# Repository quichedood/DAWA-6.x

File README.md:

# DAWA-6.x - FR (See below for US)

Site web officiel (FR) : http://dawa.panik-po.com/

DAWA est un système de chronométrage et d'acquisition de données pour votre moto.
Il enregistre les données 10x par seconde dans un fichier CSV.

# Q&A rapide
* __Comment sont récupérées les données ?__  
Pas de prise OBD, protocole trop lent sur ma "veille" moto de 2009. Je récupère les informations directement sur le faisceau du calculateur.
Chaque moto est différente, il faudra sur une autre moto :
    - Identifier les signaux (RPM, vitesse, position poignée de gaz, rapport engagé et frein)
    - Vérifier la forme des signaux (RPM = signal carré, poignée de gaz = signal analogique, etc.)
    - Eventuellement adapter le code au niveau de la programmation si le signal est complètement différent

* __Je peux l'assembler moi même ?__  
Aucun problème, attention néanmoins, il vous faut au minimum :
    - Le circuit imprimé (je peux le fournir, j'en ai quelques uns en stock)
    - Un programmateur pour les 2 µproc Atmel SAMD21 (Atmel ICE BASIC par exemple)
    - Une station de soudure à l'air chaud (indispensable pour souder l'IMU)

* __Combien ça coute ?__  
Grossièrement, voici ce que ça me coûte :
    - PCB : ~10€
    - Composants : ~90€
    - Autres (impression 3D, résine pour les sondes de t°, la journée passée à assembler un exemplaire) : à vous de juger

Certes, ça reste moins cher que ce que l'on peut trouver dans le commerce (Starlane, Alfano, 3DMS) mais ce n'est clairement pas comparable.  
Vous voulez un vrai chrono, utilisable à la sortie de sa boite, passez votre chemin et dirigez vous vers les produits du commerce.  
Vous voulez un maximum de fonctionnalités, pouvoir faire évoluer un projet libre et avez quelques notions en électronique/développement, ce projet est pour vous :)

# Les nouveautés de la v6
* __Nouveau circuit imprimé__ : DAWA v6 est désormais un circuit imprimé autonome (puce Atmel SAMD21 comme l'Arduino M0). La v5 était un module qui se branchait sur un Arduino M0
* __Nouveau capteur de position__ : Le capteurs 9 axes MPU-9250 est maintenant utilisé. Ce capteur est monté sur un circuit imprimé secondaire avec son propre µproc (Atmel SAMD21)
* __Nouvel écran OLED__ : Un peu plus grand (1.3" vs 0.96"). Le connecteur d’écran (SPI) est compatible avec les écrans LCD couleur 2,4" 240x320
* __Nouveau boitier__ : Un tout nouveau boîtier imprimé en 3D
* __Autodetection des capteurs__ : Les capteurs de température infrarouges sont maintenant détectés automatiquement
* __Navigation__ : Ajout d'un système de menu de navigation et 4 boutons pour permettre la configuration et l'utilisation sans smartphone ni Bluetooth
* __LEDs__ : Ajout de 4 LEDs pour des événements spécifiques (meilleur temps au tour par exemple)
* __Connecteurs__ : tous les connecteurs sont maintenant du même côté (en bas), le connecteur GPS est maintenant de type SMA (à visser)
* __Batterie GPS__ : Batterie rechargeable LIR 2025

# Quelles informations sont enregistrées ?
* __Acquisition de données bruts__ : Sur les motos Triumph et beaucoup d’autres, les valeurs du calculateur peuvent être lues directement (j’utilise personnellement: RPM, vitesse, position poignée de gaz, rapport engagé et frein)
* __Atitude de la moto__ : Un capteur à 9 axes (MPU-9250) est utilisé pour stocker les G et j'espère que bientôt, le roulis et le tangage
* __Position de la moto__ : Une puce GPS UBLOX 10Hz récupère les coordonnées GPS en temps réel
* __Température infrarouge__ : Vous pouvez brancher jusqu'à 6 capteurs de température infrarouge (pneus ou t° au sol, par exemple).
* __Entrées additionnelles__ : Vous pouvez mesurer 2 entrées analogiques et 2 entrées numériques supplémentaires (capteurs de suspension par exemple)

# Où est-ce enregistré ?
Tout est stocké sur une carte micro SD.  
10 fois par seconde, une nouvelle ligne est créée dans un fichier CSV. Cette ligne contient toutes les valeurs de données séparées par un point-virgule.  
Les valeurs actuelles sont affichées en temps réel sur l’écran OLED joint.

# Peut-il être utilisé comme un chronomètre ?
OUI ! Depuis la v4 et l'intégration d'une puce GPS 10Hz, des fonctions de chronométrage sont disponibles.

# Comment ça marche ?
Rien de plus simple !  
Un bouton pour démarrer l'enregistrement et un pour l'arrêter :)  
Un fichier CSV est créé à chaque nouvel enregistrement.  

# Qu'en est-il des fonctions de chronométrage
Un peu plus compliqué, vous devez mettre un fichier nommé "TRACKS.CSV" sur la carte SD.  
Ce fichier contiendra le nom du circuit et les coordonnées de la ligne d'arrivée, une ligne par circuit:  
`<trackname>;<finishline lat. A>;<finishline lon. A>;<finishline lat. B>;<finishline lon. B>`  
`CAROLE;489799930;25224350;489800230;25226330`  
Pour conserver la précision, la latitude et la longitude doivent être converties en nombres entiers (multiplier par 10 000 000).  
Au début de l’enregistrement, la piste la plus proche est automatiquement choisie.

# Vous avez dit Bluetooth?
La connexion Bluetooth est utile dans ces 2 cas:  
- Vous venez de terminer votre session sur piste et vous voulez connaître les temps/meilleurs tours  
- Avant d'utiliser DAWA, certains paramètres peuvent être ajustés, utilisez la console Bluetooth pour les configurer !  
  
J'utilise "Serial Bluetooth Terminal" sur Androïd. Connectez-vous et tapez "help" pour voir toutes les commandes disponibles

# Evolutions
* __Temps intermédiaire__ : Ajout de la gestion des temps intermédiaires

# Bugs connus
* __Angle d'inclinaison__ : Le composant est présent, l'algorithme aussi mais les valeurs dérivent dans le temps. C'est une problématique récurrente.

# Contenu du référentiel
* /3D Case - Pièces Fusion 360 et fichiers STL pour l'impression 3D
* /Arduino - Le fichier .ino que vous devez insérer dans l’Arduino M0
* /Documentation - Quelques informations sur ce projet (FR)
* /Eagle - Tous les fichiers Eagle (schémas, PCB/Gerber, bibliothèques, liste de composants)

# DAWA-6.x - US

French official website project : http://dawa.panik-po.com/

DAWA is an Arduino datalogger and laptimer for your motorbike.
It records 10 times per seconds in a CSV file lots of information.

# What's new in v6
* __New PCB__ : DAWA v6 is now a standalone PCB (Atmel SAMD21 chip like Arduino M0). v5 was a shield which needs an Arduino M0
* __New IMU__ : MPU-9250 is now used. This IMU is on a secondary PCB with his own µproc (Atmel SAMD21)
* __New OLED screen__ : A little bit bigger (1.3" vs 0.96"). The screen connector (SPI) is compatible with 2.4" 240x320 color LCD
* __New enclosure__ : A brand new 3D printed enclosure
* __Sensors autodetection__ : Infrared temperature sensors are now autodetected
* __Navigation__ : Add a navigation menu system and 4 buttons to allow configuration and use without smartphone and Bluetooth
* __Lights__ : Add 4 LEDS for specific events (best time on lap for example)
* __Connectors__ : All connectors are now on the same side (bottom), GPS connector is now SMA
* __GPS battery__ : Rechargeable LIR 2025 Battery

# What information is logged ?
* __Raw data acquisition__ : On Triumph bikes and many others, ECU values can be directly read (I personnaly use : RPM, SPEED, GEAR POSITION, THROTTLE and BRAKE state)
* __Environement values__ : A 9-axis sensor (MPU-9250) is used to store G-forces and I hope soon, roll and pitch
* __Position values__ : A UBLOX 10Hz GPS chip gets realtime coordinates
* __Infrared temperatures__ : You can plug up to 6 infrared temperature sensors (tyres or ground t° for example)
* __Additional inputs__ : You can measure 2 analog inputs and 2 digital inputs (suspension sensors for exemple)

# Where is it logged ?
Everything is stored on a micro SD card.  
10 times per seconds, a new line is created in a CSV file. This line contains every data values separated by a semicolon.  
Current values are displayed in realtime on the OLED screen attached.

# Could it be used as a laptimer ?
YES ! Since v4 and the integration of a 10Hz GPS chip, laptimer functions are available.

# How does it work ?
I couldn't make it easier !  
Press the button start recording, press again stop recording :)  
One CSV file is created on each new record.

# What about laptimer functions
A little bit more difficult, you have to put a file named "TRACKS.CSV" on the sdcard.  
This file will contain track name and finishline coordinates, one line per track :  
`<trackname>;<finishline lat. A>;<finishline lon. A>;<finishline lat. B>;<finishline lon. B>`  
`CAROLE;489799930;25224350;489800230;25226330`  
To keep precision, latitude and longitude should be converted to integers (multiply by 10 000 000).  
When start recording the closer track is automatically chosen.

# You said Bluetooth ?
Bluetooth connection is usefull in these 2 cases :
- You just finish your track session and want to know lap times / best lap
- Before using DAWA, some parameters could be adjusted, use the bluetooth console to setup them !

I'm using "Serial Bluetooth Terminal" on Androïd. Connect and type "help" to view all available commands

# What's next  
* __Laptimer split time__ : Add split time management

# Known bugs
* __Lean angle__ : Seems easy but in fact very complicated to obtain good values without drift

# Repository Contents
* /3D Case - Fusion 360 parts and STL files for 3D printing
* /Arduino - The .ino file you need to put in the Arduino M0
* /Documentation - Some brief explanations about this shield (french - not translated)
* /Eagle - All Eagle files (schematics, PCB/Gerber, libraries, parts list)

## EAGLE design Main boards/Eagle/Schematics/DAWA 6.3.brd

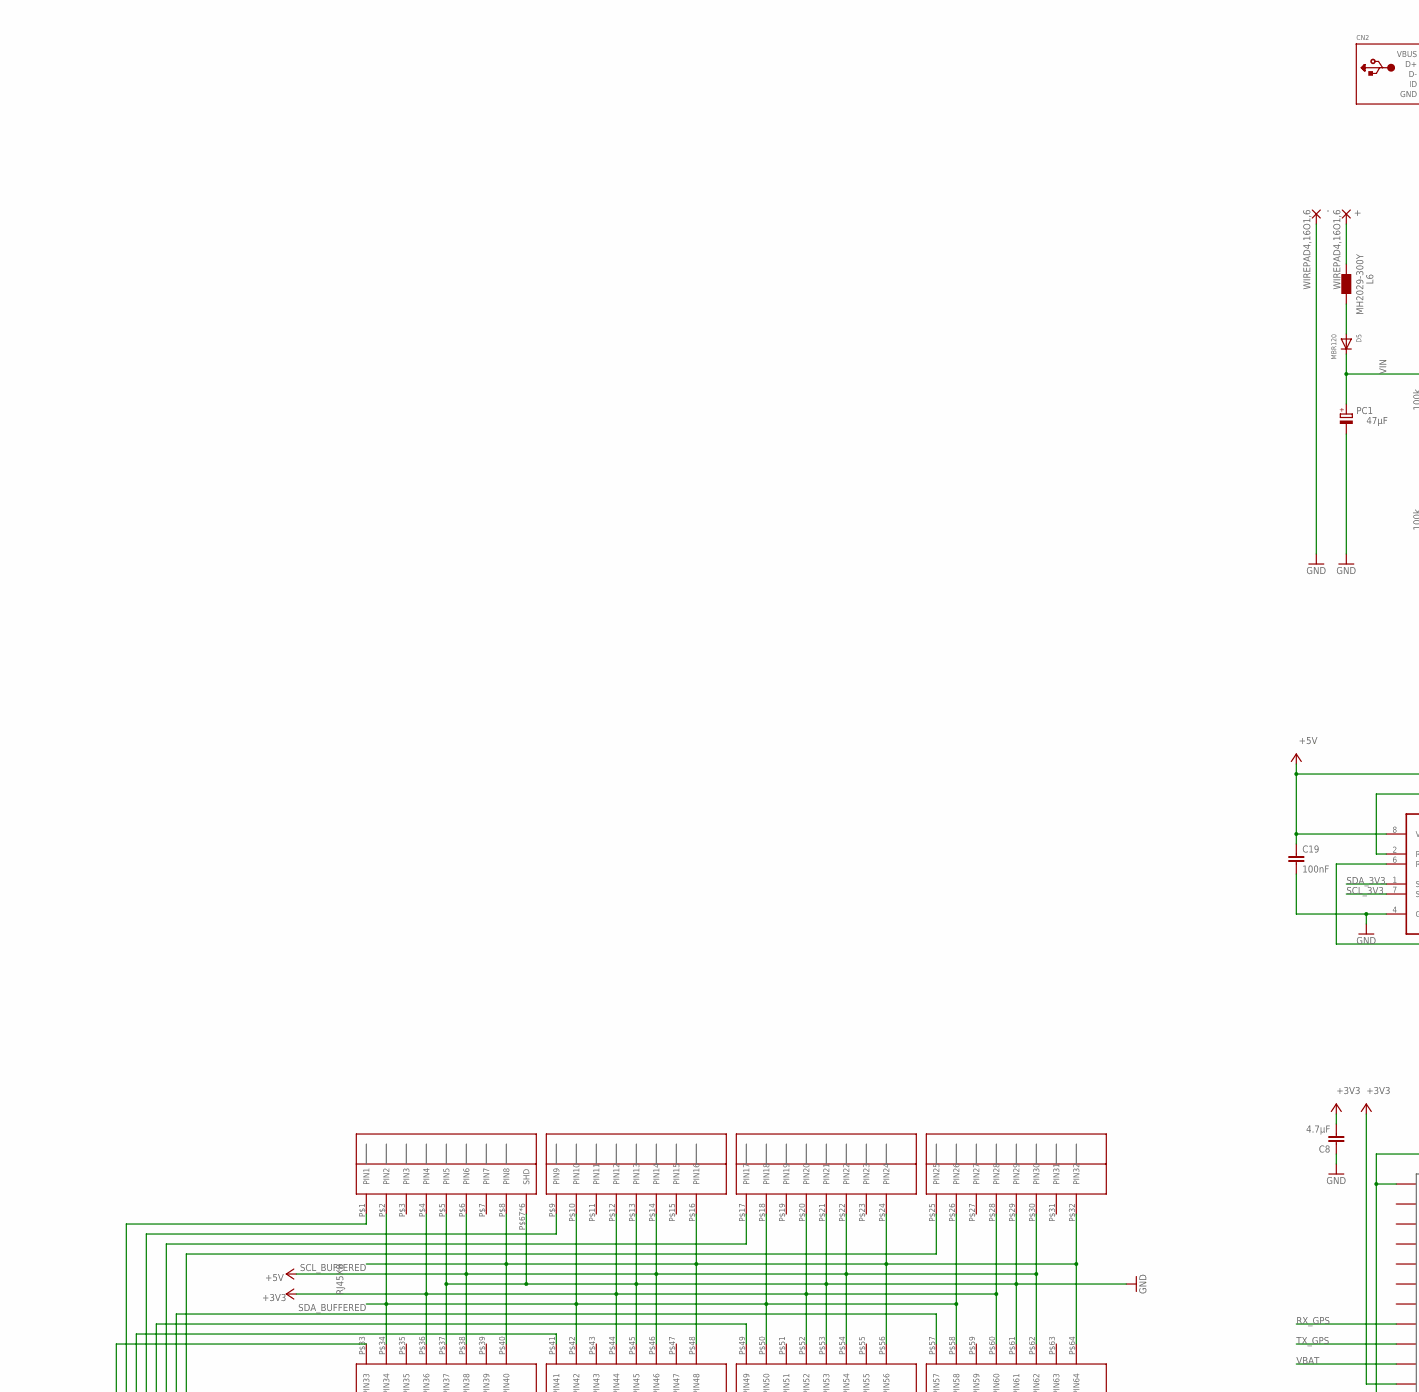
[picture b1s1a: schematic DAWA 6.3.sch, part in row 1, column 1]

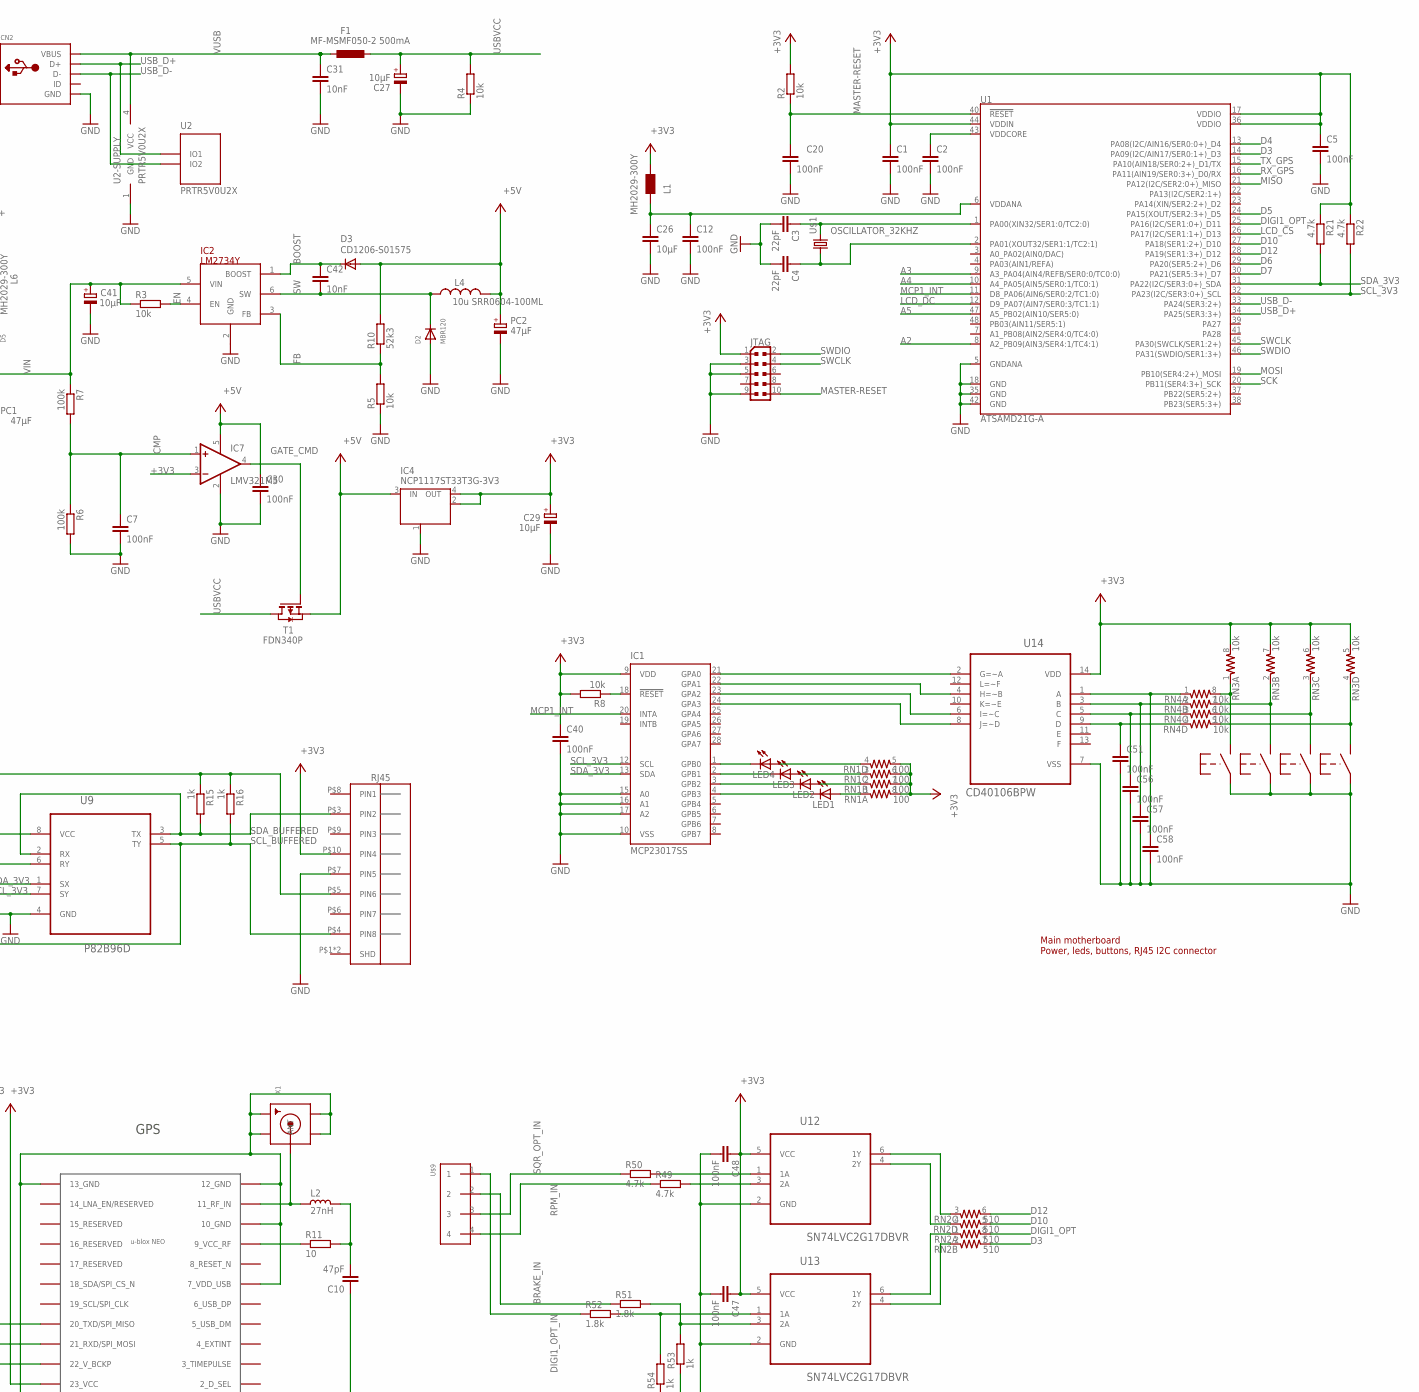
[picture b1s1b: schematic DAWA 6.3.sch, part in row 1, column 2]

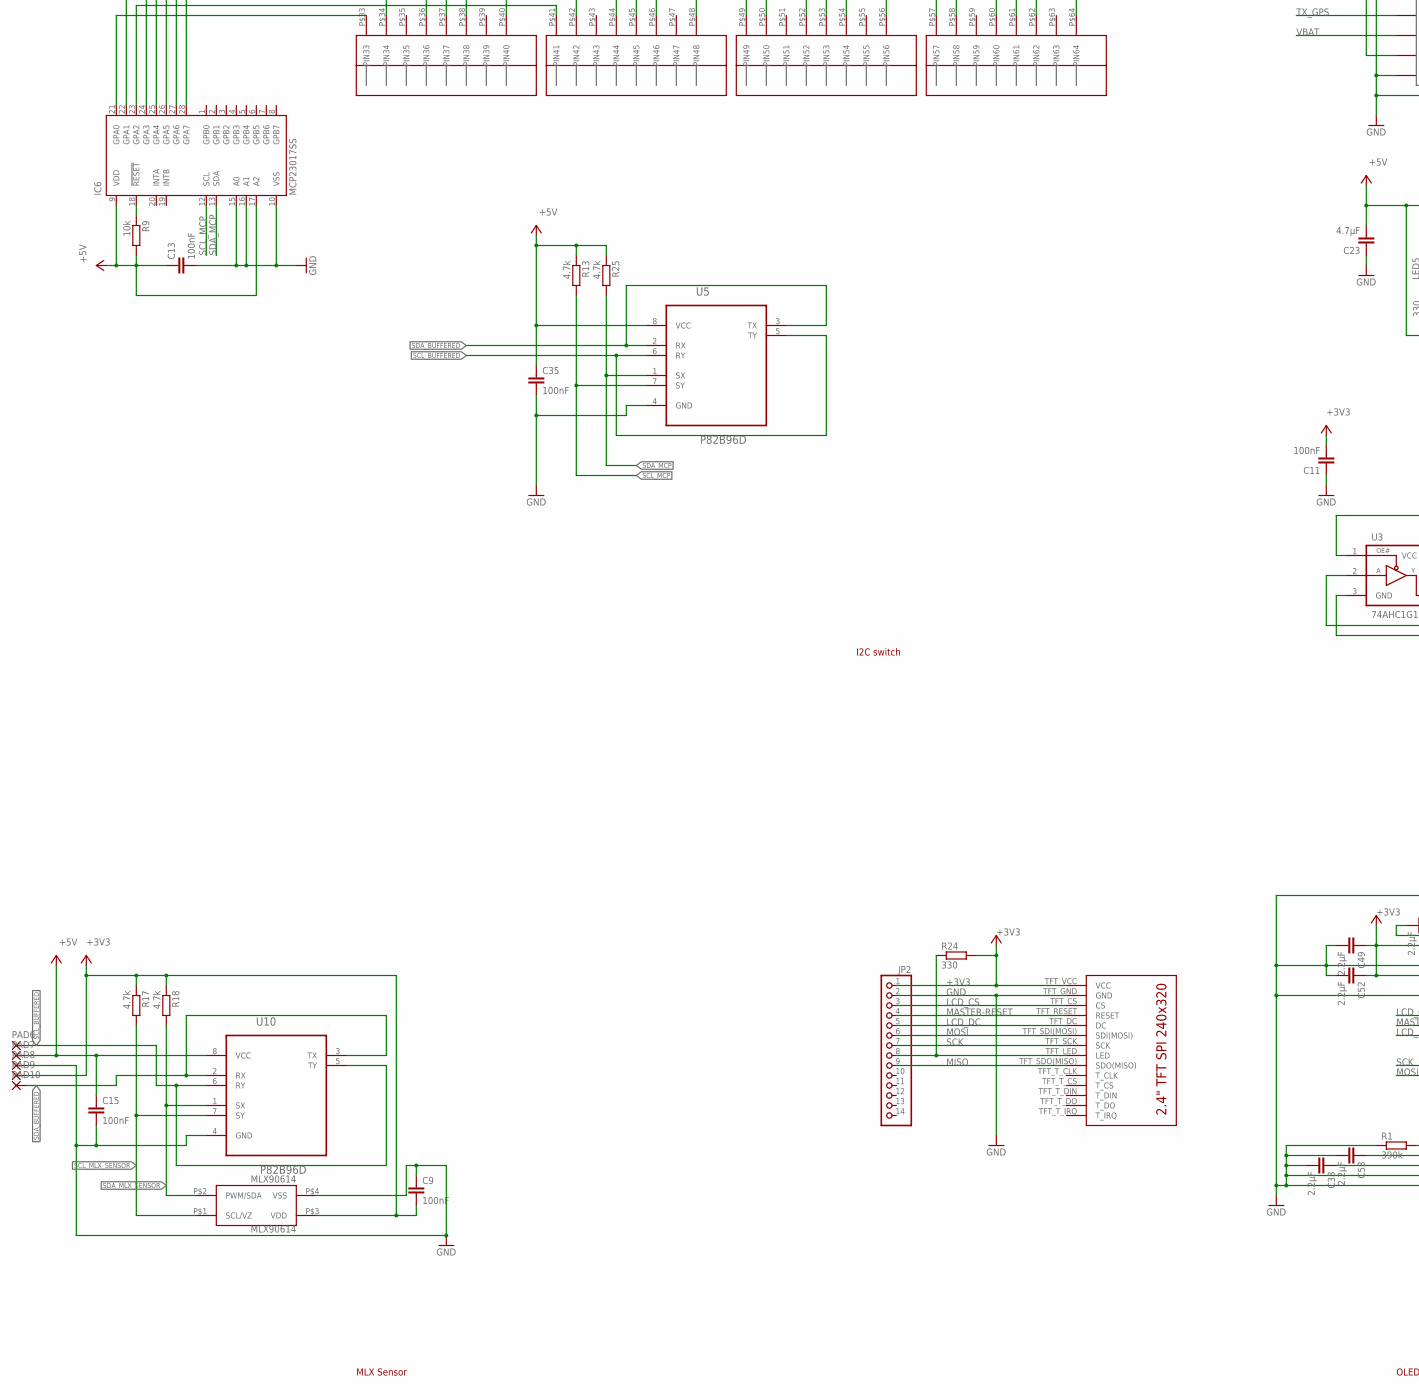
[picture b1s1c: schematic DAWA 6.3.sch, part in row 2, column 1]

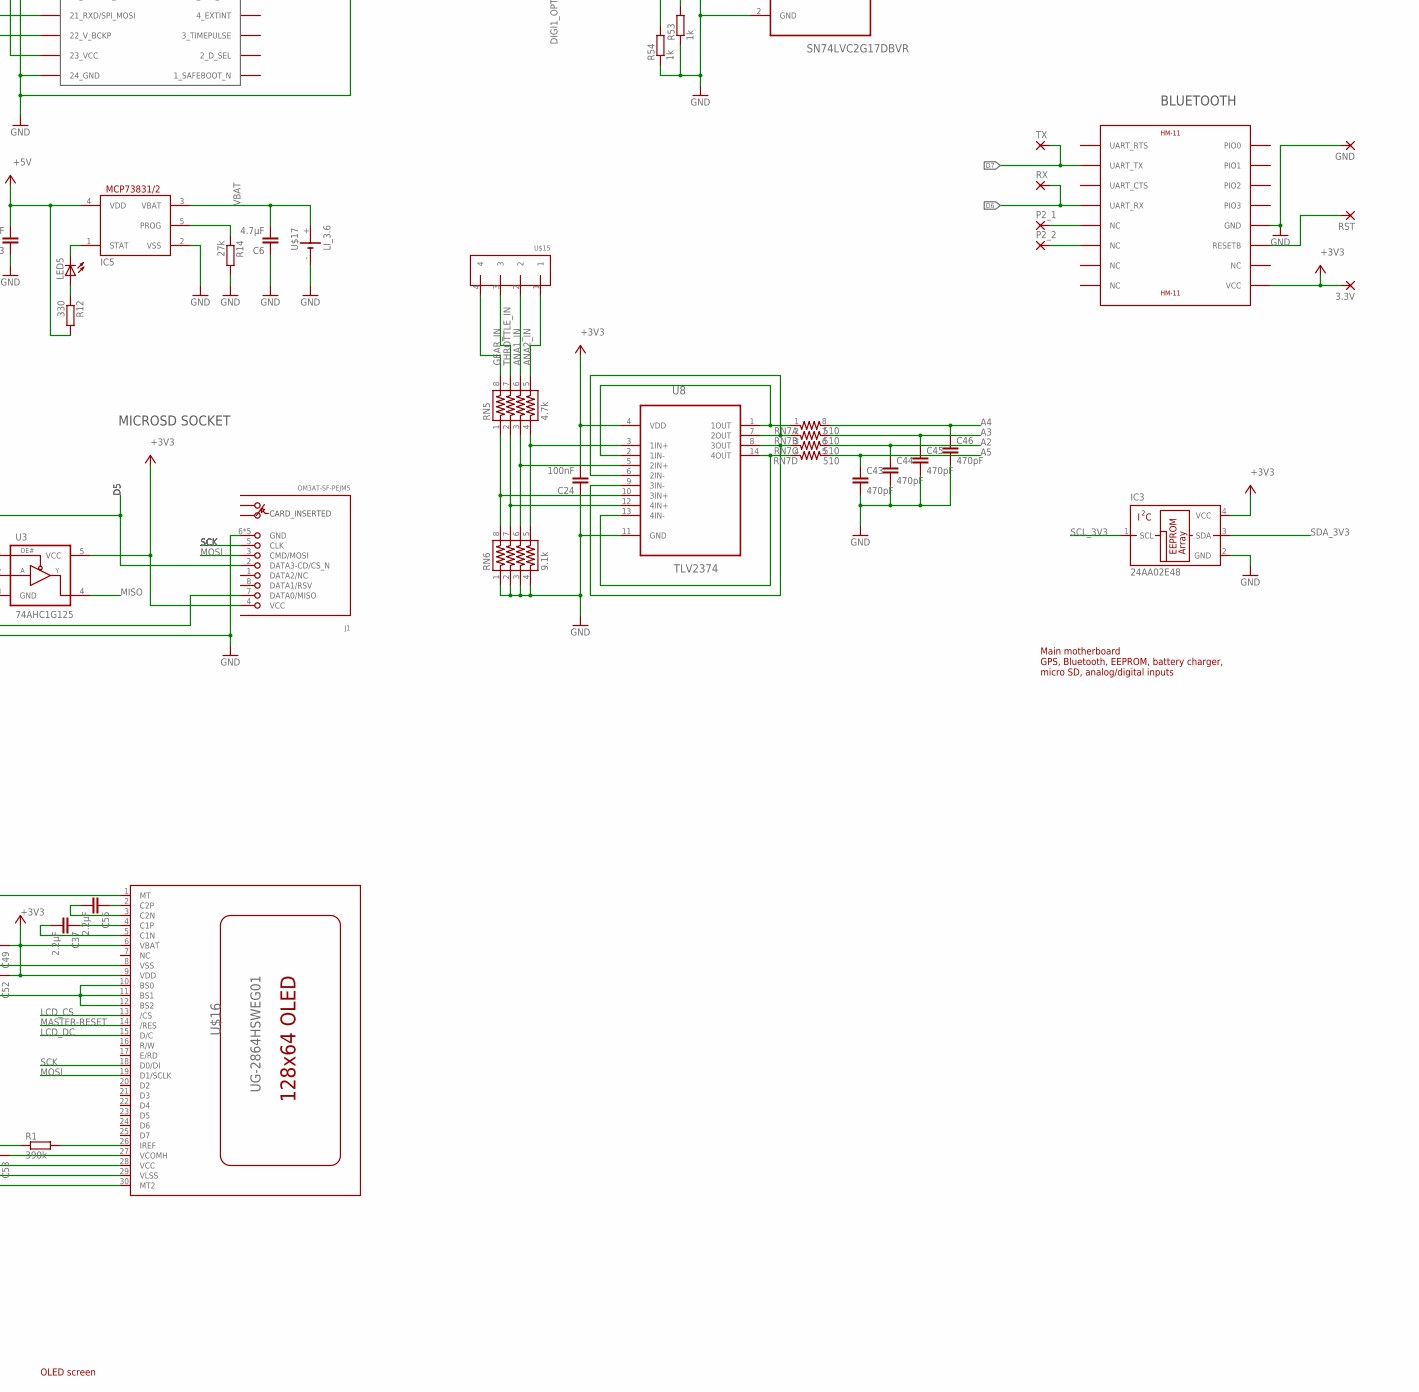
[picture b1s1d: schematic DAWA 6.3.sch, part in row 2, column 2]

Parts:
3.3V: WIREPADSMD1,27-254; SMD1,27-2,54
+: WIREPAD4,16O1,6; 4,16O1,6
-: WIREPAD4,16O1,6; 4,16O1,6
C1, C2, C5, C7, C9, C11, C12, C13, C15, C19, C20, C24, C30, C35, C40, C47, C48, C51, C56, C57, C58: 100nF; C0603
C3, C4: 22pF; C0603
C6, C8, C23: 4.7µF; C0603
C10: 47pF; C0603
C26: 10µF; C0805
C27, C29, C41: 10µF; SMC_B
C31, C42: 10nF; C0603
C33, C37, C49, C52, C53, C55: 2.2µF; C0603
C43, C44, C45, C46: 470pF; C0603
CN2: USB; USB-MINIB-DAWA
D2, D5: MBR120; SOD-123FL
D3: CD1206-S01575; MINIMELF
F1: MF-MSMF050-2 500mA; L1812
GND: WIREPADSMD1,27-254; SMD1,27-2,54
IC1, IC6: MCP23017SS; SSOP28
IC2: LM2734Y; SOT23-6
IC3: 24AA02E48; SOT23-5L
IC4: NCP1117ST33T3G-3V3; SOT223
IC5: MCP73831/OT; SOT23-5L
IC7: LMV321M5; SOT23-5
J1: DM3AT-SF-PEJM5
JP2: PINHD-1X14-CB; 1X14-CB
JTAG: PINHEAD_PINHD-2X5PASSO127; PINHEAD_2X05_127
L1, L6: MH2029-300Y; 0805
L2: 27nH; L0603
L4: 10u SRR0604-100ML; SRR0604
LED1, LED2, LED3, LED4, LED5: LEDCHIPLED_1206; CHIPLED_1206
MLX90614: MLX90614; TO-39
P2_1, P2_2: WIREPADSMD1,27-254; SMD1,27-2,54
PAD6, PAD7, PAD8, PAD9, PAD10: WIREPAD1,6/0,9; 1,6/0,9
PC1, PC2: 47µF; PANASONIC_D
R1: 390k; R0603
R2, R3, R4, R5, R8, R9: 10k; R0603
R6, R7: 100k; R0603
R10: 52k3; R0603
R11: 10; R0603
R12, R24: 330; R0603
R13, R17, R18, R21, R22, R25, R49, R50: 4.7k; R0603
R14: 27k; R0603
R15, R16, R53, R54: 1k; R0603
R51, R52: 1.8k; R0603
RJ45_MAIN_BOARD: RJ45
RN1: 100; 742-8NS
RN2, RN7: 510; 742-8NS
RN3, RN4: 10k; 742-8NS
RN5: 4.7k; 742-8NS
RN6: 9.1k; 742-8NS
RST: WIREPADSMD1,27-254; SMD1,27-2,54
RX: WIREPADSMD1,27-254; SMD1,27-2,54
T1: FDN340P; SOT-23
TX: WIREPADSMD1,27-254; SMD1,27-2,54
U1: ATSAMD21G-A; TQFP-48
U2: PRTR5V0U2X; SOT-143B
U3: 74AHC1G125; SOT23-5
U5, U9, U10: P82B96D; SOIC127P600X175-8N
U8: TLV2374; SOP65P640X120-14N
U12, U13: SN74LVC2G17DBVR; SOT95P280X145-6N
U14: CD40106BPW; SOP65P640X120-14N
U$1: OSCILLATOR_32KHZ; OSCILLATOR_SMD
U$2: HM-11
U$3: NEO-M8
U$4: TFT_2.4
U$5, U$6, U$7, U$8: SKPMAPE10
U$9, U$15: 4_PIN_JST-XH-SMD
U$16: UG-2864HSWEG01; 1X30-0.7MM
U$17: LI_3.6
U$18: RJ45X8
X1: SMACONNECTOR_EDGE; SMA_EDGELAUNCH

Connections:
+3V3: 3.3V.1, C1.1, C5.1, C8.2, C9.2, C11.2, C24.2, C29.+, C40.1, C47.1, C48.1, C49.1, C52.1, IC1.9 (VDD), IC3.4 (VCC), IC4.2 (OUT), IC4.4 (OUT), IC7.3 (-IN), J1.4 (VCC), JP2.1, JTAG.1, L1.1, MLX90614.P$3 (VDD), PAD9.1, R2.2, R8.2, R17.1, R18.1, R21.1, R22.1, R24.2, RJ45_MAIN_BOARD.P$10 (PIN4), RN1.5 (2), RN1.6 (2), RN1.7 (2), RN1.8 (2), RN3.5 (2), RN3.6 (2), RN3.7 (2), RN3.8 (2), U1.17 (VDDIO), U1.36 (VDDIO), U1.44 (VDDIN), U3.5 (VCC), U8.4 (VDD), U12.5 (VCC), U13.5 (VCC), U14.14 (VDD), U$2.VCC, U$3.23 (23_VCC), U$4.TFT_VCC (VCC), U$16.6 (VBAT), U$16.9 (VDD), U$18.P$4 (PIN4), U$18.P$12 (PIN12), U$18.P$20 (PIN20), U$18.P$28 (PIN28), U$18.P$36 (PIN36), U$18.P$44 (PIN44), U$18.P$52 (PIN52), U$18.P$60 (PIN60)
+5V: C13.1, C15.1, C19.1, C23.2, C30.1, C35.1, D3.A, IC4.3 (IN), IC5.4 (VDD), IC6.9 (VDD), IC6.17 (A2), IC7.5 (V+), L4.P$2 (2), PAD7.1, PC2.+, R9.2, R10.2, R12.2, R13.1, R15.1, R16.1, R25.1, RJ45_MAIN_BOARD.P$5 (PIN6), T1.2 (S), U5.8 (VCC), U9.8 (VCC), U10.8 (VCC), U$18.P$6 (PIN6), U$18.P$14 (PIN14), U$18.P$22 (PIN22), U$18.P$30 (PIN30), U$18.P$38 (PIN38), U$18.P$46 (PIN46), U$18.P$54 (PIN54), U$18.P$62 (PIN62)
A2: C44.1, RN7.6 (2), U1.8 (A2_PB09(AIN3/SER4:1/TC4:1))
A3: C45.1, RN7.7 (2), U1.9 (A3_PA04(AIN4/REFB/SER0:0/TC0:0))
A4: C46.1, RN7.8 (2), U1.10 (A4_PA05(AIN5/SER0:1/TC0:1))
A5: C43.1, RN7.5 (2), U1.47 (A5_PB02(AIN10/SER5:0))
ALIM+: +.1, L6.2
ANA1_IN: RN5.6, U$15.2
ANA2_IN: RN5.5, U$15.1
BOOST: C42.1, D3.C, IC2.1 (BOOST)
BRAKE_IN: R51.1, U$9.2
CMP: C7.1, IC7.1 (+IN), R6.1, R7.2
D3: RN2.7 (2), U1.14 (PA09(I2C/AIN17/SER0:1+)_D3)
D4: U1.13 (PA08(I2C/AIN16/SER0:0+)_D4)
D5: J1.2 (DATA3-CD/CS_N), U1.24 (PA15(XOUT/SER2:3+)_D5), U3.1 (OE#)
D6: RX.1, U1.29 (PA20(SER5:2+)_D6), U$2.UART_RX
D7: TX.1, U1.30 (PA21(SER5:3+)_D7), U$2.UART_TX
D10: RN2.5 (2), U1.27 (PA18(SER1:2+)_D10)
D12: RN2.6 (2), U1.28 (PA19(SER1:3+)_D12)
DIGI1_OPT: RN2.8 (2), U1.25 (PA16(I2C/SER1:0+)_D11)
DIGI1_OPT_IN: R52.1, U$9.1
EN: IC2.4 (EN), R3.2
FB: IC2.3 (FB), R5.2, R10.1
GATE_CMD: IC7.4 (OUT), T1.3 (G)
GEAR_IN: RN5.8, U$15.4
GND: -.1, C1.2, C2.2, C3.2, C4.2, C5.2, C6.1, C7.2, C8.1, C9.1, C10.1, C11.1, C12.2, C13.2, C15.2, C19.2, C20.2, C23.1, C24.1, C26.2, C27.-, C29.-, C30.2, C31.2, C33.2, C35.2, C40.2, C41.-, C43.2, C44.2, C45.2, C46.2, C47.2, C48.2, C49.2, C51.2, C52.2, C53.2, C56.2, C57.2, C58.2, CN2.GND, CN2.GND1 (GND), CN2.GND2 (GND), D2.A, GND.1, IC1.10 (VSS), IC1.15 (A0), IC1.16 (A1), IC1.17 (A2), IC2.2 (GND), IC3.2 (GND), IC4.1 (GND/ADJ), IC5.2 (VSS), IC6.10 (VSS), IC6.15 (A0), IC6.16 (A1), IC7.2 (V-), J1.6 (GND), J1.MOUNT0 (GND), J1.MOUNT1 (GND), J1.MOUNT2 (GND), J1.MOUNT3 (GND), JP2.2, JTAG.3, JTAG.5, JTAG.9, MLX90614.P$4 (VSS), PAD8.1, PC1.-, PC2.-, R1.1, R4.1, R5.1, R6.2, R14.2, R53.1, R54.1, RJ45_MAIN_BOARD.P$7 (PIN5), RN6.1, RN6.2, RN6.3, RN6.4, U1.5 (GNDANA), U1.18 (GND), U1.35 (GND), U1.42 (GND), U2.1 (GND), U3.3 (GND), U5.4 (GND), U8.11 (GND), U9.4 (GND), U10.4 (GND), U12.2 (GND), U13.2 (GND), U14.7 (VSS), U$2.GND, U$3.7 (7_VDD_USB), U$3.10 (10_GND), U$3.12 (12_GND), U$3.13 (13_GND), U$3.24 (24_GND), U$4.TFT_GND (GND), U$5.P$1, U$6.P$1, U$7.P$1, U$8.P$1, U$16.1 (MT), U$16.8 (VSS), U$16.10 (BS0), U$16.11 (BS1), U$16.12 (BS2), U$16.29 (VLSS), U$16.30 (MT2), U$17.-, U$18.P$5 (PIN5), U$18.P$13 (PIN13), U$18.P$21 (PIN21), U$18.P$29 (PIN29), U$18.P$37 (PIN37), U$18.P$45 (PIN45), U$18.P$53 (PIN53), U$18.P$61 (PIN61), U$18.P$67 (SHD), U$18.P$68 (SHD), U$18.P$69 (SHD), U$18.P$70 (SHD), U$18.P$71 (SHD), U$18.P$72 (SHD), X1.GND@1 (GND4), X1.GND@2 (GND3), X1.GND@3 (GND2), X1.GND@4 (GND1)
LCD_CS: JP2.3, U1.26 (PA17(I2C/SER1:1+)_D13), U$4.TFT_CS (CS), U$16.13 (/CS)
LCD_DC: JP2.5, U1.12 (D9_PA07(AIN7/SER0:3/TC1:1)), U$4.TFT_DC (DC), U$16.15 (D/C)
MASTER-RESET: C20.1, JP2.4, JTAG.10, R2.1, U1.40 (!RESET!), U$4.TFT_RESET (RESET), U$16.14 (/RES)
MCP1_INT: IC1.20 (INTA), U1.11 (D8_PA06(AIN6/SER0:2/TC1:0))
MISO: JP2.9, U1.21 (PA12(I2C/SER2:0+)_MISO), U3.4 (Y), U$4.TFT_SDO(MISO) (SDO(MISO))
MOSI: J1.3 (CMD/MOSI), JP2.6, U1.19 (PB10(SER4:2+)_MOSI), U$4.TFT_SDI(MOSI) (SDI(MOSI)), U$16.19 (D1/SCLK)
unnamed: C2.1, U1.43 (VDDCORE)
unnamed: C3.1, U1.1 (PA00(XIN32/SER1:0/TC2:0)), U$1.2
unnamed: C4.1, U1.2 (PA01(XOUT32/SER1:1/TC2:1)), U$1.1
unnamed: RN5.4, RN6.5, U8.3 (1IN+)
unnamed: IC1.1 (GPB0), LED4.C
unnamed: IC5.1 (STAT), LED5.C
unnamed: IC1.2 (GPB1), LED3.C
unnamed: LED5.A, R12.1
unnamed: D5.A, L6.1
unnamed: C10.2, L2.1, R11.2
unnamed: IC5.5 (PROG), R14.1
unnamed: J1.7 (DATA0/MISO), U3.2 (A)
unnamed: P2_1.1, U$2.NC@5 (NC)
unnamed: RST.1, U$2.RESETB
unnamed: P2_2.1, U$2.NC@6 (NC)
unnamed: R11.1, U$3.9 (9_VCC_RF)
unnamed: L2.2, U$3.11 (11_RF_IN), X1.P (ANT)
unnamed: RN5.3, RN6.6, U8.5 (2IN+)
unnamed: IC1.3 (GPB2), LED2.C
unnamed: IC1.4 (GPB3), LED1.C
unnamed: RN7.1, U8.1 (1OUT), U8.2 (1IN-)
unnamed: RN7.2 (1), U8.6 (2IN-), U8.7 (2OUT)
unnamed: RN7.3 (1), U8.8 (3OUT), U8.9 (3IN-)
unnamed: RN7.4 (1), U8.13 (4IN-), U8.14 (4OUT)
unnamed: RN5.2, RN6.7, U8.12 (4IN+)
unnamed: LED4.A, RN1.4 (1)
unnamed: LED3.A, RN1.3 (1)
unnamed: RN5.1, RN6.8, U8.10 (3IN+)
unnamed: LED2.A, RN1.2 (1)
unnamed: LED1.A, RN1.1
unnamed: IC1.18 (!RESET), R8.1
unnamed: IC6.28 (GPA7), U$18.P$25 (PIN25)
unnamed: RN2.3 (1), U12.6 (1Y)
unnamed: RN3.4 (1), RN4.5 (2), U$5.P$2
unnamed: RN3.3 (1), RN4.6 (2), U$6.P$2
unnamed: IC6.26 (GPA5), U$18.P$17 (PIN17)
unnamed: IC6.24 (GPA3), U$18.P$9 (PIN9)
unnamed: R50.2, U12.1 (1A)
unnamed: R49.2, U12.3 (2A)
unnamed: R51.2, R53.2, U13.3 (2A)
unnamed: R52.2, R54.2, U13.1 (1A)
unnamed: RN2.1, U13.6 (1Y)
unnamed: RN2.2 (1), U13.4 (2Y)
unnamed: JP2.8, R24.1, U$4.TFT_LED (LED)
unnamed: RN2.4 (1), U12.4 (2Y)
unnamed: RN3.1, RN4.8 (2), U$8.P$2
unnamed: RN3.2 (1), RN4.7 (2), U$7.P$2
unnamed: IC6.22 (GPA1), U$18.P$1 (PIN1)
unnamed: IC6.21 (GPA0), U$18.P$33 (PIN33)
unnamed: IC6.23 (GPA2), U$18.P$41 (PIN41)
unnamed: IC6.25 (GPA4), U$18.P$49 (PIN49)
unnamed: IC6.27 (GPA6), U$18.P$57 (PIN57)
unnamed: IC6.18 (!RESET), R9.1
unnamed: IC1.21 (GPA0), U14.2 (G=~A)
unnamed: IC1.22 (GPA1), U14.4 (H=~B)
unnamed: R1.2, U$16.26 (IREF)
unnamed: C55.1, U$16.2 (C2P)
unnamed: C55.2, U$16.3 (C2N)
unnamed: C37.1, U$16.4 (C1P)
unnamed: C37.2, U$16.5 (C1N)
unnamed: C33.1, U$16.28 (VCC)
unnamed: C53.1, U$16.27 (VCOMH)
unnamed: IC1.23 (GPA2), U14.6 (I=~C)
unnamed: IC1.24 (GPA3), U14.8 (J=~D)
unnamed: C51.1, RN4.4 (1), U14.9 (D)
unnamed: C56.1, RN4.3 (1), U14.5 (C)
unnamed: C57.1, RN4.2 (1), U14.3 (B)
unnamed: C58.1, RN4.1, U14.1 (A)
RPM_IN: R49.1, U$9.4
RX_GPS: U1.16 (PA11(AIN19/SER0:3+)_D0/RX), U$3.20 (20_TXD/SPI_MISO)
SCK: J1.5 (CLK), JP2.7, U1.20 (PB11(SER4:3+)_SCK), U$4.TFT_SCK (SCK), U$16.18 (D0/DI)
SCL_3V3: IC1.12 (SCL), IC3.1 (SCL), R22.2, U1.32 (PA23(I2C/SER3:0+)_SCL), U9.7 (SY)
SCL_BUFFERED: PAD6.1, R16.2, RJ45_MAIN_BOARD.P$4 (PIN8), U5.5 (TY), U5.6 (RY), U9.5 (TY), U9.6 (RY), U10.5 (TY), U10.6 (RY), U$18.P$8 (PIN8), U$18.P$16 (PIN16), U$18.P$24 (PIN24), U$18.P$32 (PIN32), U$18.P$40 (PIN40), U$18.P$48 (PIN48), U$18.P$56 (PIN56), U$18.P$64 (PIN64)
SCL_MCP: IC6.12 (SCL), R13.2, U5.7 (SY)
SCL_MLX_SENSOR: MLX90614.P$1 (SCL/VZ), R17.2, U10.7 (SY)
SDA_3V3: IC1.13 (SDA), IC3.3 (SDA), R21.2, U1.31 (PA22(I2C/SER3:0+)_SDA), U9.1 (SX)
SDA_BUFFERED: PAD10.1, R15.2, RJ45_MAIN_BOARD.P$3 (PIN2), U5.2 (RX), U5.3 (TX), U9.2 (RX), U9.3 (TX), U10.2 (RX), U10.3 (TX), U$18.P$2 (PIN2), U$18.P$10 (PIN10), U$18.P$18 (PIN18), U$18.P$26 (PIN26), U$18.P$34 (PIN34), U$18.P$42 (PIN42), U$18.P$50 (PIN50), U$18.P$58 (PIN58)
SDA_MCP: IC6.13 (SDA), R25.2, U5.1 (SX)
SDA_MLX_SENSOR: MLX90614.P$2 (PWM/SDA), R18.2, U10.1 (SX)
SQR_OPT_IN: R50.1, U$9.3
SW: C42.2, D2.C, IC2.6 (SW), L4.P$1 (1)
SWCLK: JTAG.4, U1.45 (PA30(SWCLK/SER1:2+))
SWDIO: JTAG.2, U1.46 (PA31(SWDIO/SER1:3+))
THROTTLE_IN: RN5.7, U$15.3
TX_GPS: U1.15 (PA10(AIN18/SER0:2+)_D1/TX), U$3.21 (21_RXD/SPI_MOSI)
USBVCC: C27.+, F1.1, R4.2, T1.1 (D)
USB_D+: CN2.D+, U1.34 (PA25(SER3:3+)), U2.2 (IO1)
USB_D-: CN2.D-, U1.33 (PA24(SER3:2+)), U2.3 (IO2)
VBAT: C6.2, IC5.3 (VBAT), U$3.22 (22_V_BCKP), U$17.+
VDDANA: C12.1, C26.1, L1.2, U1.6 (VDDANA)
VIN: C41.+, D5.C, IC2.5 (VIN), PC1.+, R3.1, R7.1
VUSB: C31.1, CN2.VBUS, F1.2, U2.4 (VCC)

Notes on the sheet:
GPS
MICROSD SOCKET
BLUETOOTH
MLX Sensor
OLED screen
I2C switch
Main motherboard Power, leds, buttons, RJ45 I2C connector
Main motherboard GPS, Bluetooth, EEPROM, battery charger, micro SD, analog/digital inputs

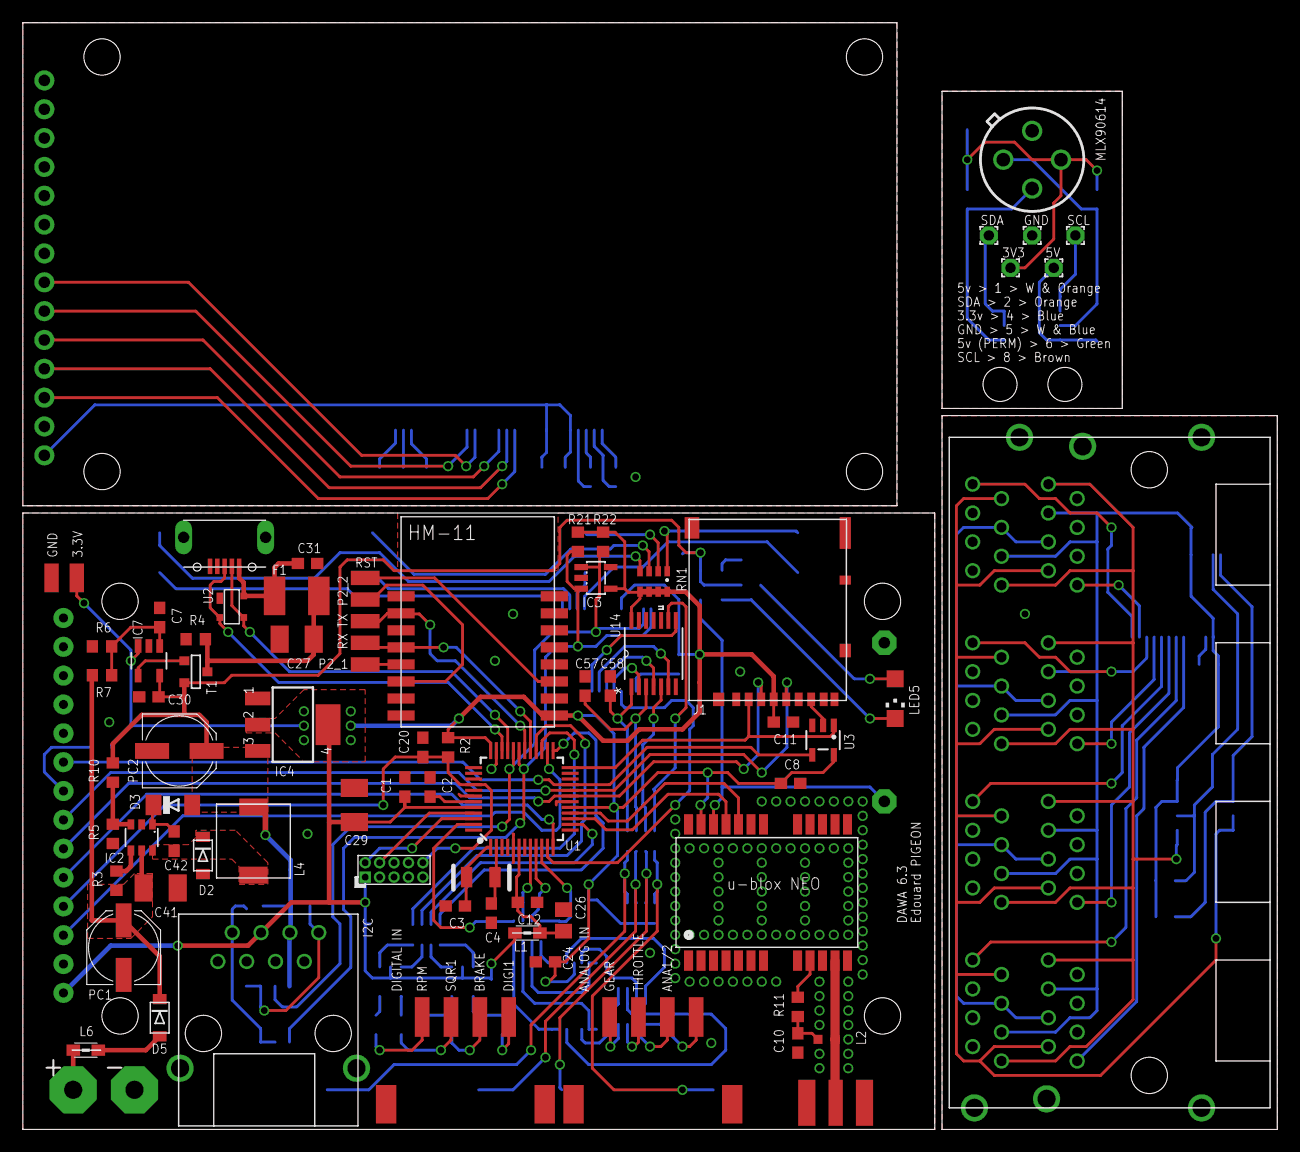
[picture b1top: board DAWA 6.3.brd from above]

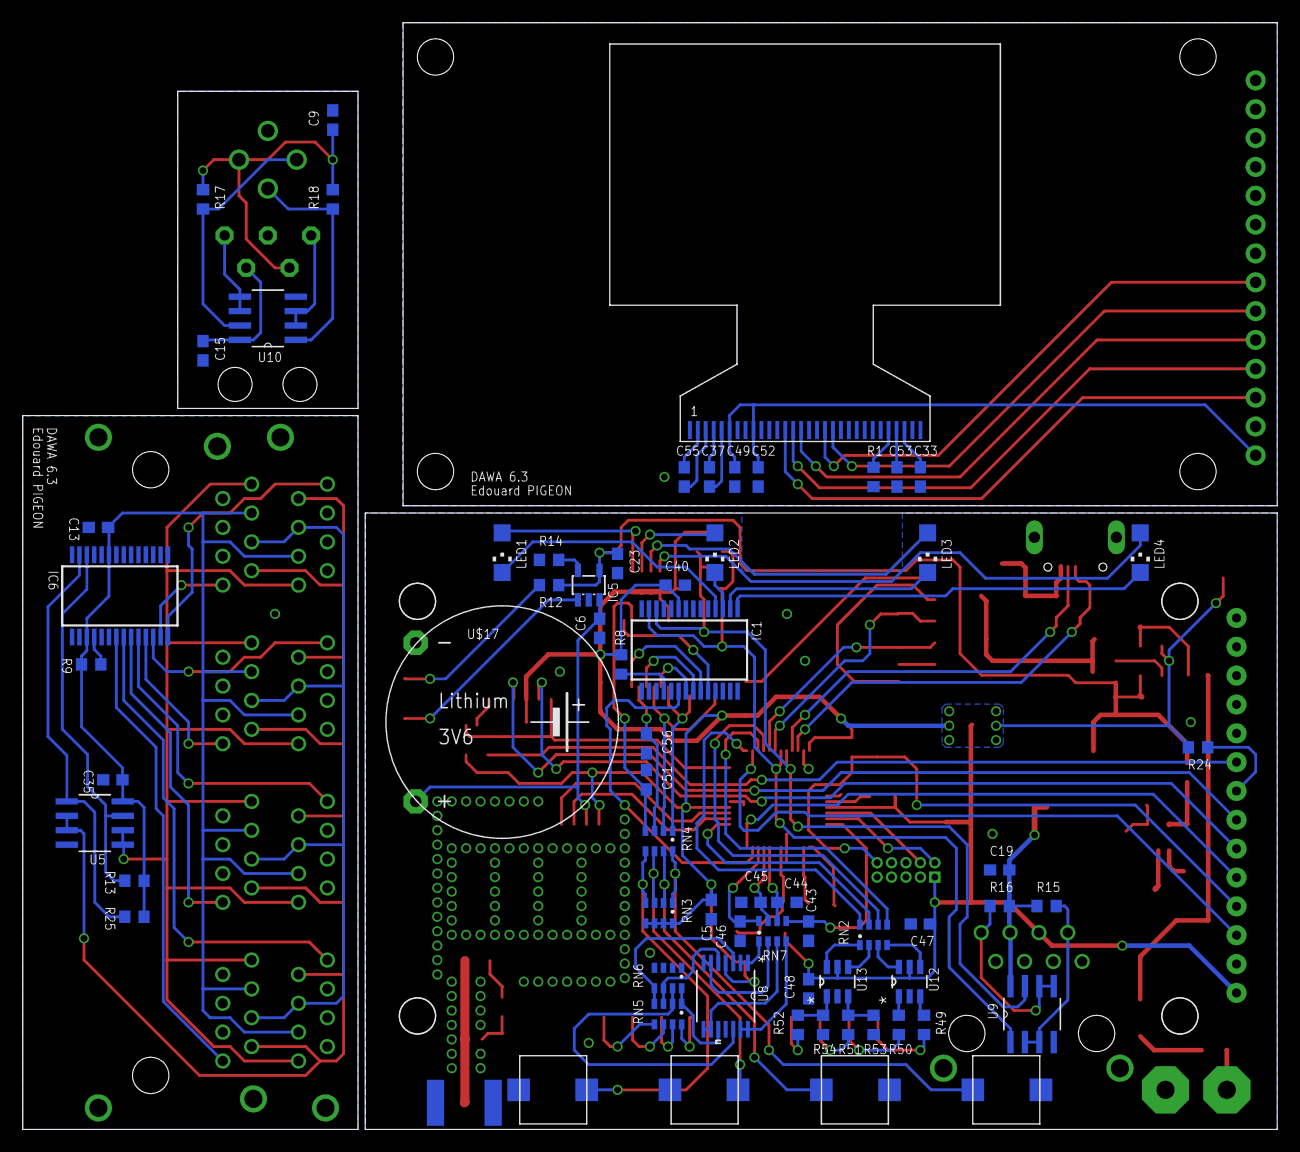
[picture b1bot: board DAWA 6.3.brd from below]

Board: 2 copper layers, 110.5 x 97.5 mm, 145 parts (67 on the bottom side), 123 nets.

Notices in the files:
parts and their libraries:
microbuilder: This work is placed in the public domain, and may be freely used for commercial and non-commercial work with the following conditions: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
SparkFun-Switches: Licensing: Creative Commons ShareAlike 4.0 International - https://creativecommons.org/licenses/by-sa/4.0
